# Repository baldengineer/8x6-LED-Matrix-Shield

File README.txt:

Full Information:  http://www.cmiyc.com/projects/led-matrix-arduino-shield/

Eagle Project files and example code to create a 8x6 LED Matrix Shield for an Arduino Duemilanove / Uno.  (May also work on a Leonardo.)

-James Enginerd
www.cmiyc.com
byerly0503@gmail.com

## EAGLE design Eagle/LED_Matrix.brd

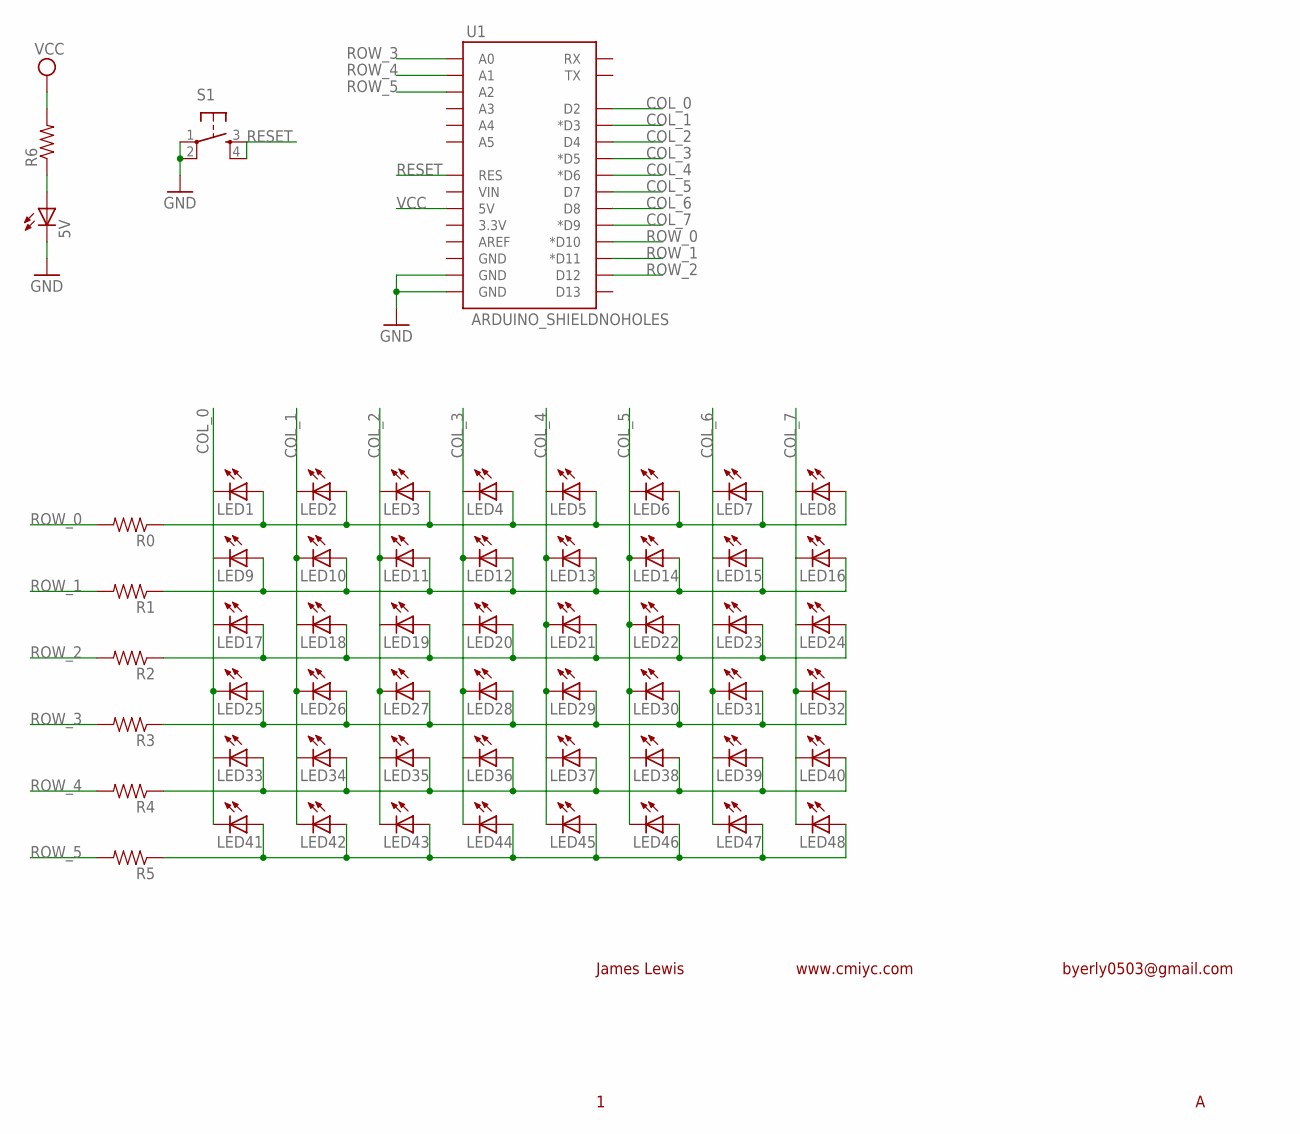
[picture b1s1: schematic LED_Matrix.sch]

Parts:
5V: LED1206; LED-1206
LED1, LED2, LED3, LED4, LED5, LED6, LED7, LED8, LED9, LED10, LED11, LED12, LED13, LED14, LED15, LED16, LED17, LED18, LED19, LED20, LED21, LED22, LED23, LED24, LED25, LED26, LED27, LED28, LED29, LED30, LED31, LED32, LED33, LED34, LED35, LED36, LED37, LED38, LED39, LED40, LED41, LED42, LED43, LED44, LED45, LED46, LED47, LED48: LED5MM
R0, R1, R2, R3, R4, R5, R6: RESISTOR1206; 1206
S1: TAC_SWITCHSMD; TACTILE_SWITCH_SMD
U1: ARDUINO_SHIELDNOHOLES; DUEMILANOVE_SHIELD_NOHOLES

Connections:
COL_0: LED1.K (C), LED9.K (C), LED17.K (C), LED25.K (C), LED33.K (C), LED41.K (C), U1.D2
COL_1: LED2.K (C), LED10.K (C), LED18.K (C), LED26.K (C), LED34.K (C), LED42.K (C), U1.D3 (*D3)
COL_2: LED3.K (C), LED11.K (C), LED19.K (C), LED27.K (C), LED35.K (C), LED43.K (C), U1.D4
COL_3: LED4.K (C), LED12.K (C), LED20.K (C), LED28.K (C), LED36.K (C), LED44.K (C), U1.D5 (*D5)
COL_4: LED5.K (C), LED13.K (C), LED21.K (C), LED29.K (C), LED37.K (C), LED45.K (C), U1.D6 (*D6)
COL_5: LED6.K (C), LED14.K (C), LED22.K (C), LED30.K (C), LED38.K (C), LED46.K (C), U1.D7
COL_6: LED7.K (C), LED15.K (C), LED23.K (C), LED31.K (C), LED39.K (C), LED47.K (C), U1.D8
COL_7: LED8.K (C), LED16.K (C), LED24.K (C), LED32.K (C), LED40.K (C), LED48.K (C), U1.D9 (*D9)
GND: 5V.C, S1.1, S1.2, U1.GND@0 (GND), U1.GND@1 (GND)
unnamed: LED41.A, LED42.A, LED43.A, LED44.A, LED45.A, LED46.A, LED47.A, LED48.A, R5.1
unnamed: 5V.A, R6.1
OLD_1: LED1.A, LED2.A, LED3.A, LED4.A, LED5.A, LED6.A, LED7.A, LED8.A, R0.1
OLD_2: LED9.A, LED10.A, LED11.A, LED12.A, LED13.A, LED14.A, LED15.A, LED16.A, R1.1
OLD_3: LED17.A, LED18.A, LED19.A, LED20.A, LED21.A, LED22.A, LED23.A, LED24.A, R2.1
OLD_4: LED25.A, LED26.A, LED27.A, LED28.A, LED29.A, LED30.A, LED31.A, LED32.A, R3.1
OLD_5: LED33.A, LED34.A, LED35.A, LED36.A, LED37.A, LED38.A, LED39.A, LED40.A, R4.1
RESET: S1.3, S1.4, U1.RES
ROW_0: R0.2, U1.D10 (*D10)
ROW_1: R1.2, U1.D11 (*D11)
ROW_2: R2.2, U1.D12
ROW_3: R3.2, U1.A0
ROW_4: R4.2, U1.A1
ROW_5: R5.2, U1.A2
VCC: R6.2, U1.5V

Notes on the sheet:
James Lewis
www.cmiyc.com
byerly0503@gmail.com

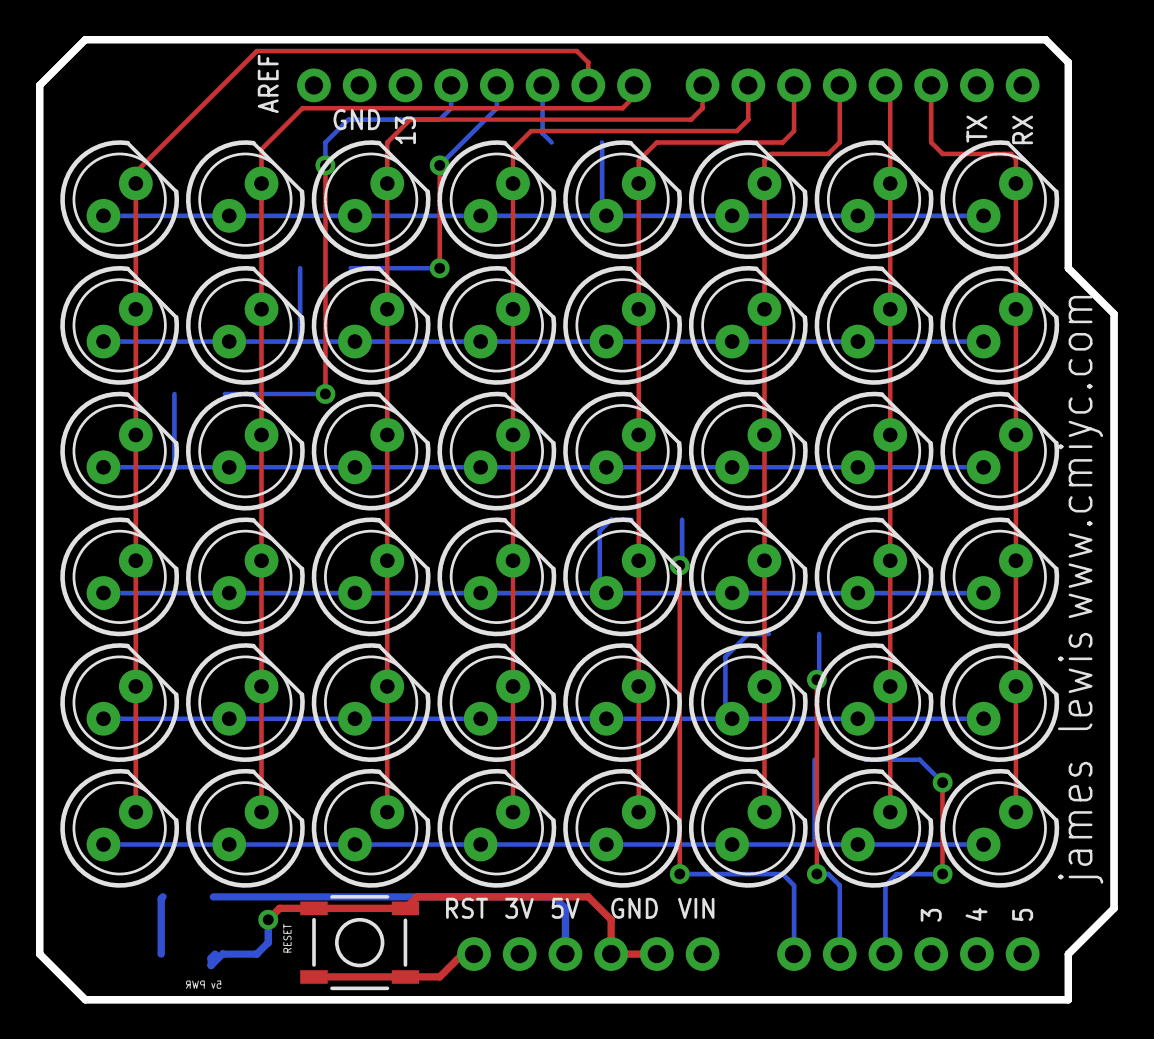
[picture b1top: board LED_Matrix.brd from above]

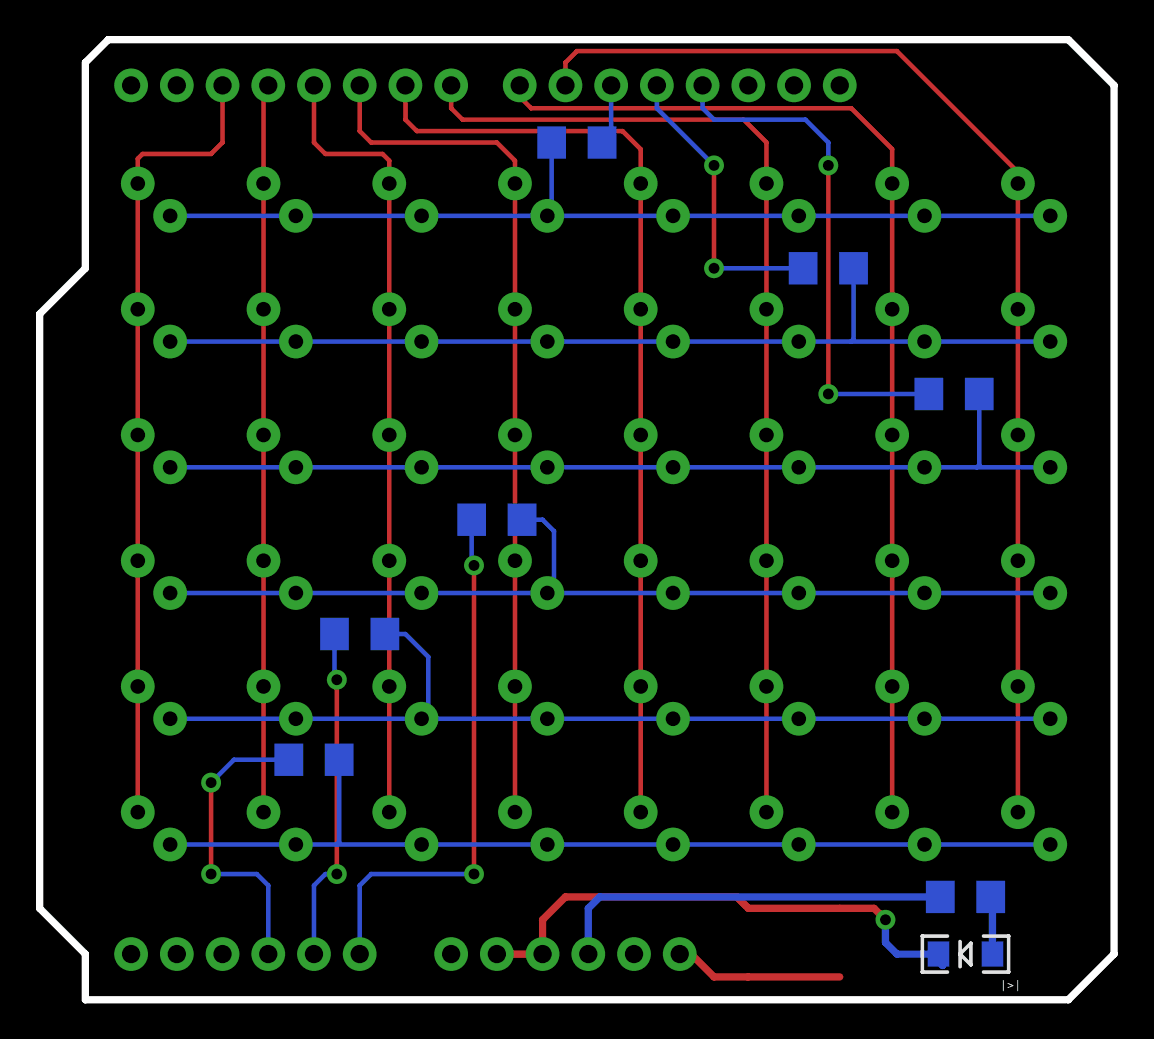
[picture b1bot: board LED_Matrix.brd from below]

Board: 2 copper layers, 59.7 x 53.3 mm, 58 parts (8 on the bottom side), 24 nets.

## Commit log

2012-10-06 Changed "hardware" to "eagle"
    Trying to stick with a convention. Eagle refers to design files.
    Hardware should refer to enclosures.
